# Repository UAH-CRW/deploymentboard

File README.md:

# deploymentboard
Deployment electronics design

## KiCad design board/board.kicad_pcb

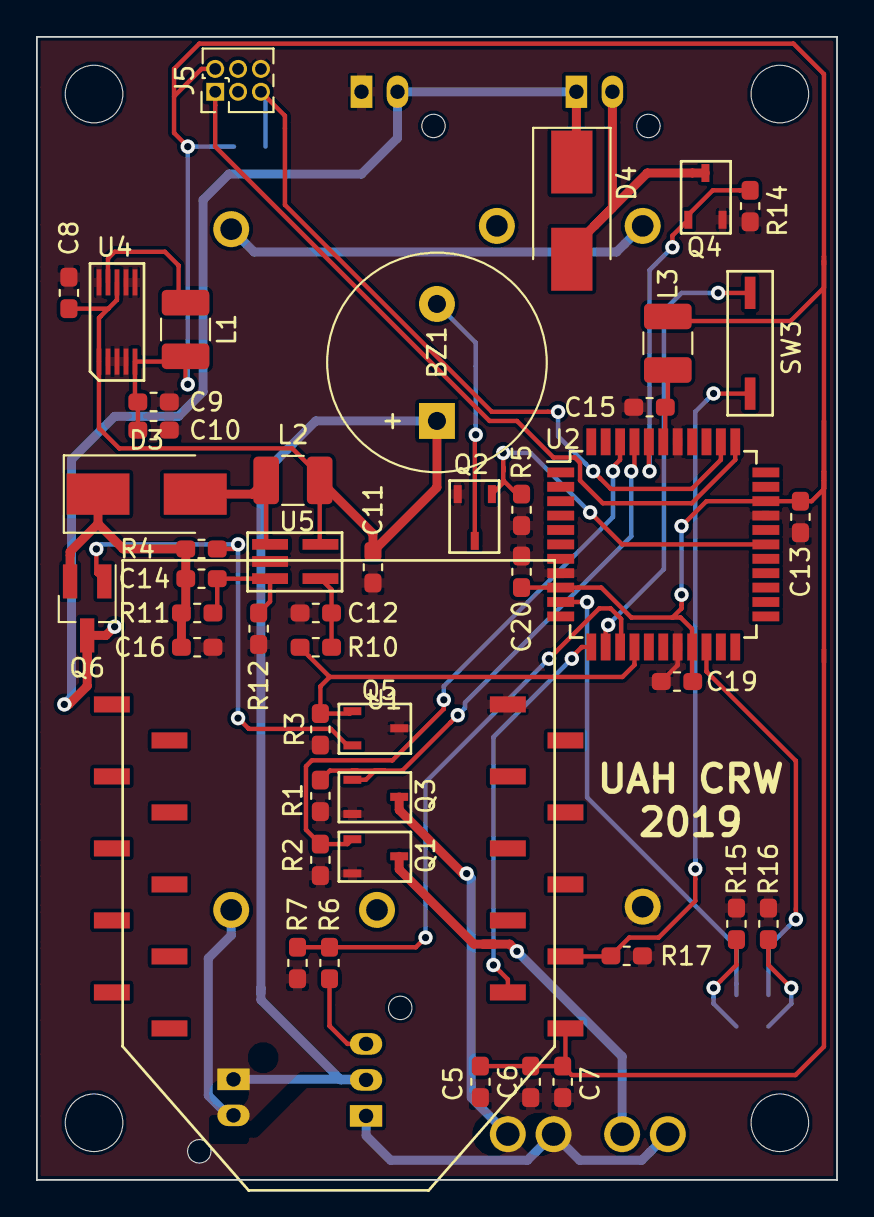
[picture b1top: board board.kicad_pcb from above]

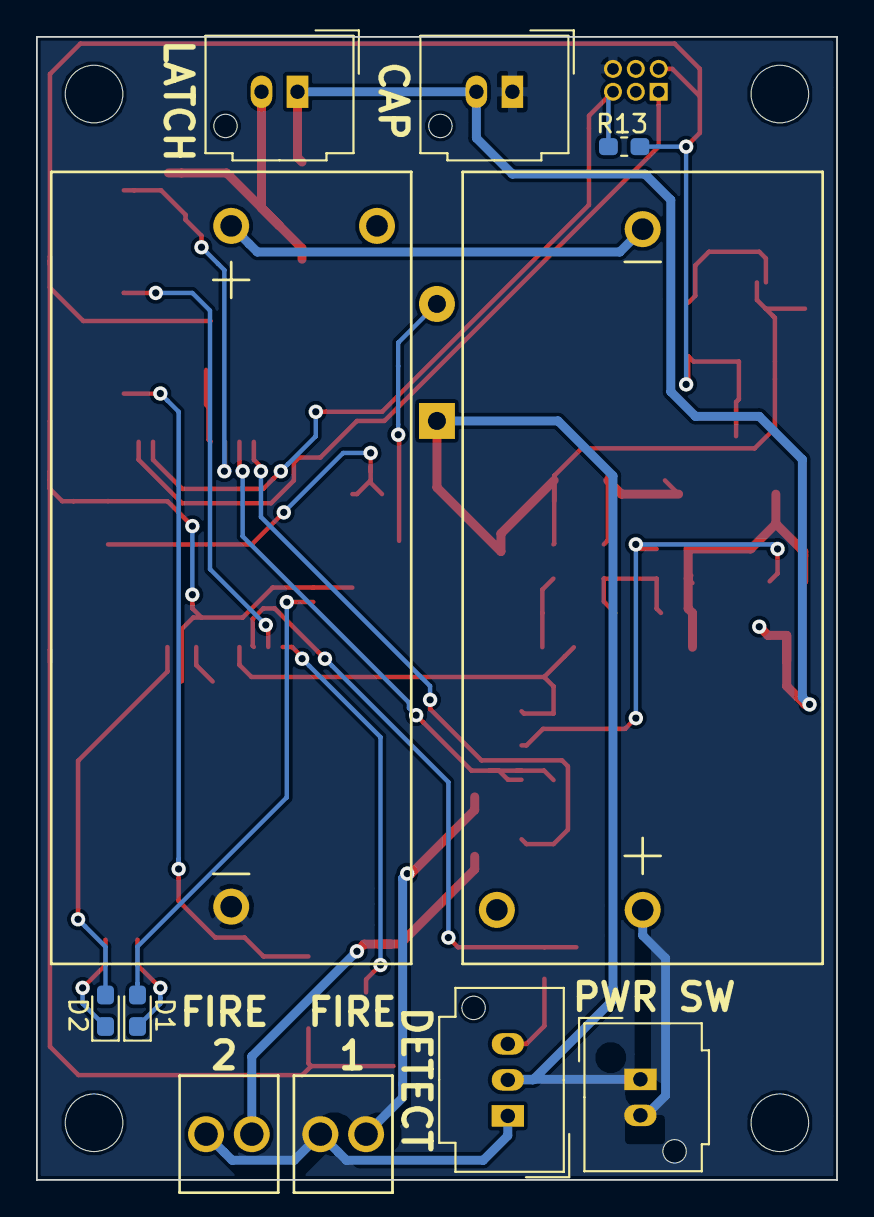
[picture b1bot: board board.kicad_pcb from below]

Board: 2 copper layers, 44.4 x 63.5 mm, 61 parts (11 on the bottom side), 34 nets.

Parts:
BT1, BT2: Battery; CR123A Battery Holder
BZ1: Buzzer; Buzzer_12x9.5RM7.6
C5, C8, C10: 10uF; C_0603_1608Metric_Pad1.05x0.95mm_HandSolder
C6, C11, C12: 1uF; C_0603_1608Metric_Pad1.05x0.95mm_HandSolder
C7: 47pF; C_0603_1608Metric_Pad1.05x0.95mm_HandSolder
C9: 22uF; C_0603_1608Metric_Pad1.05x0.95mm_HandSolder
C13, C15, C19, C20: 100nF; C_0603_1608Metric_Pad1.05x0.95mm_HandSolder
C14: 15pF; C_0603_1608Metric_Pad1.05x0.95mm_HandSolder
C16: 4.7uF; C_0603_1608Metric_Pad1.05x0.95mm_HandSolder
D1, D2: LED; LED_0603_1608Metric_Pad1.05x0.95mm_HandSolder
D3: D; D_SMB_Handsoldering
D4: D_Small; D_SMB_Handsoldering
J1, J3: Screw_Terminal_01x02; 2 pin 2.54mm screw terminal OSTVN02A150
J4, J6: Conn_01x02_Male; Molex_MicroClasp_55932-0210_1x02_P2.00mm_Vertical
J5: Conn_02x03_Odd_Even; PinHeader_2x03_P1.27mm_Vertical
L1: 10uH; L_1210_3225Metric_Pad1.42x2.65mm_HandSolder
L2: 4.7uH; L_1210_3225Metric_Pad1.42x2.65mm_HandSolder
L3: 27nH; L_1210_3225Metric_Pad1.42x2.65mm_HandSolder
MH1, MH2, MH3, MH4: MountingHole; MountingHole_3.2mm_M3
Q1, Q2, Q3, Q4, Q5: Q_NJFET_GSD; NFET Toshiba SSM3K339R
Q6: Q_PJFET_GSD; SOT-23_Handsoldering
R1, R2, R4, R5, R6, R7, R10, R13, R14, R17: 10k; R_0603_1608Metric_Pad1.05x0.95mm_HandSolder
R3: 10K; R_0603_1608Metric_Pad1.05x0.95mm_HandSolder
R11: 432k; R_0603_1608Metric_Pad1.05x0.95mm_HandSolder
R12: 49.9k; R_0603_1608Metric_Pad1.05x0.95mm_HandSolder
R15, R16: 220; R_0603_1608Metric_Pad1.05x0.95mm_HandSolder
SW1: SW_SPDT; Molex_MicroClasp_55932-0310_1x03_P2.00mm_Vertical
SW2: SW_SPDT; Molex_MicroClasp_55932-0210_1x02_P2.00mm_Vertical
SW3: SW_DIP_x01; DIP Switch CHS-01TA
U1: XBee; XBee_SMD
U2: ATxmega128A4U-AU; TQFP-44_10x10mm_P0.8mm
U4: IC_REG_BCK_3.3V; 10-pin FP TPS62056DGSR
U5: IC_REG_BOOST_ADJ_1.4A; IC REG BOOST SC4503TSKTRT

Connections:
+3V3: C5.2, C6.2, C7.2, C9.1, C10.1, C13.1, C19.1, C20.1, J5.2, L1.2, L3.1, R13.2, U1.1, U2.9, U2.19, U2.31, U4.5
+6V: BZ1.1, C8.1, C11.2, L2.1, SW1.2, SW2.1, U4.1, U4.8, U5.5
+12V: D4.1, J4.2, J6.1, Q6.3
/BUZZER_CTRL: Q2.1, R5.1, U2.28
/E_Match_Fire_1: Q3.1, R1.2, U2.41
/E_Match_Fire_2: Q1.1, R2.1, U2.42
/LATCH_ENABLE: Q5.1, R3.2, R10.2, U2.15
/LATCH_SENSE: R6.2, R7.2, U2.14
/LED1CTRL: D1.2, U2.10
/LED2CTRL: D2.2, U2.20
/PDI_CLK: J5.5, R13.1, U2.35
/PDI_DATA: J5.1, U2.34
/SOLENOID_CTRL: Q4.1, R14.1, U2.40
/USARTC0_RX: U1.2, U2.12
/USARTC0_TX: SW3.1, U2.13
GND: BT2.2, C5.1, C6.1, C7.1, C8.2, C9.2, C10.2, C11.1, C12.2, C13.2, C15.1, C16.2, C19.2, C20.2, J4.1, J5.6, Q1.2, Q2.2, Q3.2, Q4.2, Q5.3, R1.1, R2.2, R3.1, R5.2, R7.1, R12.2, R14.2, R15.1, R16.1, R17.2, U1.10, U2.8, U2.18, U2.30, U2.38, U4.2, U4.3, U4.4, U4.6, U4.7, U4.10, U5.2
unnamed: BT1.1, SW2.2
unnamed: BT1.2, BT2.1
unnamed: BZ1.2, Q2.3
unnamed: C12.1, R10.1, U5.4
unnamed: C14.1, C16.1, D3.1, Q6.2, R4.2, R11.1
unnamed: C14.2, R11.2, R12.1, U5.3
unnamed: C15.2, L3.2, U2.39
unnamed: D1.1, R15.2
unnamed: D2.1, R16.2
unnamed: D3.2, L2.2, U5.1
unnamed: D4.2, J6.2, Q4.3
unnamed: J1.1, Q3.3
unnamed: J1.2, J3.1, SW1.1
unnamed: J3.2, Q1.3
unnamed: L1.1, U4.9
unnamed: Q5.2, Q6.1, R4.1
unnamed: R6.1, SW1.3
unnamed: R17.1, SW3.2, U1.3

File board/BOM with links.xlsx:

Id | Designator | Package | Quantity | Designation | Supplier and ref
1 | J1,J3 | 2 pin 2.54mm screw terminal OSTVN02A150 | 2 | Screw_Terminal_01x02 | https://www.digikey.com/product-detail/en/on-shore-technolog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
2 | C20,C19,C3,C2,C1,C15,C13 | C_0603_1608Metric_Pad1.05x0.95mm_HandSolder | 7 | 100nF | https://www.digikey.com/product-detail/en/samsung-electro-me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
3 | J6 | JST_PH_B2B-PH-K_1x02_P2.00mm_Vertical | 1 | Conn_01x02_Male | https://www.digikey.com/product-detail/en/jst-sales-america-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
4 | D4 | D_SMB_Handsoldering | 1 | D_Small | https://www.digikey.com/product-detail/en/smc-diode-solution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
5 | R17,R14,R7,R13,R6,R4,R2,R1,R5,R10 | R_0603_1608Metric_Pad1.05x0.95mm_HandSolder | 9 | 10k | https://www.digikey.com/product-detail/en/susumu/RR0816P-103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
6 | SW3 | DIP Switch CHS-01TA | 1 | SW_DIP_x01 | https://www.digikey.com/product-detail/en/nidec-copal-electr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
7 | SW2 | JST_PH_B2B-PH-K_1x02_P2.00mm_Vertical | 1 | SW_SPDT | https://www.digikey.com/product-detail/en/jst-sales-america-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
8 | U1 | XBee_SMD | 2 | XBee | https://www.digikey.com/product-detail/en/sullins-connector-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
9 | C17,C18,C7 | C_0603_1608Metric_Pad1.05x0.95mm_HandSolder | 3 | 47pF | https://www.digikey.com/product-detail/en/avx-corporation/06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
10 | R15,R16 | R_0603_1608Metric_Pad1.05x0.95mm_HandSolder | 2 | 220 | https://www.digikey.com/product-detail/en/panasonic-electron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
11 | Q4,Q1,Q2,Q3 | NFET Toshiba SSM3K339R | 4 | Q_NJFET_GSD | https://www.digikey.com/product-detail/en/toshiba-semiconduc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
12 | J5 | PinHeader_2x03_P1.27mm_Vertical | 1 | Conn_02x03_Odd_Even | https://www.digikey.com/product-detail/en/sullins-connector-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
13 | BZ1 | Buzzer_12x9.5RM7.6 | 1 | Buzzer | https://www.digikey.com/product-detail/en/pui-audio-inc/AT-1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
14 | C10,C8,C5 | C_0603_1608Metric_Pad1.05x0.95mm_HandSolder | 3 | 10uF | https://www.digikey.com/product-detail/en/samsung-electro-me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
15 | C4,C16 | C_0603_1608Metric_Pad1.05x0.95mm_HandSolder | 2 | 4.7uF | https://www.digikey.com/product-detail/en/samsung-electro-me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
16 | C14 | C_0603_1608Metric_Pad1.05x0.95mm_HandSolder | 1 | 15pF | https://www.digikey.com/product-detail/en/yageo/CC0603JRNPO9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
17 | C12 | C_0603_1608Metric_Pad1.05x0.95mm_HandSolder | 1 | 1uF | https://www.digikey.com/product-detail/en/samsung-electro-me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
18 | C11,C6 | C_0603_1608Metric_Pad1.05x0.95mm_HandSolder | 2 | 1uF | https://www.digikey.com/product-detail/en/samsung-electro-me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
19 | C9 | C_0603_1608Metric_Pad1.05x0.95mm_HandSolder | 1 | 22uF | https://www.digikey.com/product-detail/en/samsung-electro-me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
20 | SW1 | JST_EH_B03B-EH-A_1x03_P2.50mm_Vertical | 1 | SW_SPDT | https://www.digikey.com/product-detail/en/jst-sales-america-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
21 | J2 | USB_Micro-B_Amphenol_10103594-0001LF_Horizontal | 1 | USB_B_Micro | https://www.digikey.com/product-detail/en/molex-llc/10516400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
22 | D3 | D_SOD-323 | 1 | D | https://www.digikey.com/product-detail/en/vishay-semiconduct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
23 | L1 | L_1210_3225Metric_Pad1.42x2.65mm_HandSolder | 1 | 10uH | https://www.digikey.com/product-detail/en/taiyo-yuden/LBC322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
24 | L2 | L_1210_3225Metric_Pad1.42x2.65mm_HandSolder | 1 | 4.7uH | https://www.digikey.com/product-detail/en/murata-electronics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
25 | L3 | L_1210_3225Metric_Pad1.42x2.65mm_HandSolder | 1 | 27nH | https://www.digikey.com/product-detail/en/tdk-corporation/NL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
26 | D1 | LED_0603_1608Metric_Pad1.05x0.95mm_HandSolder | 1 | LED - green | https://www.digikey.com/product-detail/en/rohm-semiconductor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
27 | D2 | LED_0603_1608Metric_Pad1.05x0.95mm_HandSolder | 1 | LED - red | https://www.digikey.com/product-detail/en/rohm-semiconductor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
28 | U3 | SSOP-16_3.9x4.9mm_P0.635mm | 1 | FT230XS | https://www.digikey.com/product-detail/en/ftdi-future-techno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
29 | R12 | R_0603_1608Metric_Pad1.05x0.95mm_HandSolder | 1 | 49.9k | https://www.digikey.com/product-detail/en/panasonic-electron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
30 | R11 | R_0603_1608Metric_Pad1.05x0.95mm_HandSolder | 1 | 432k | https://www.digikey.com/product-detail/en/yageo/RC0603FR-074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
31 | R9,R8 | R_0603_1608Metric_Pad1.05x0.95mm_HandSolder | 2 | 27 | https://www.digikey.com/product-detail/en/rohm-semiconductor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
32 | R3 | R_0603_1608Metric_Pad1.05x0.95mm_HandSolder | 1 | 47k | https://www.digikey.com/product-detail/en/yageo/RC0603JR-074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
33 | U4 | 10-pin FP TPS62056DGSR | 1 | IC_REG_BCK_3.3V | https://www.digikey.com/product-detail/en/texas-instruments/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
34 | BT1,BT2 | CR123A Battery Holder | 2 | Battery | https://www.digikey.com/product-detail/en/keystone-electroni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
35 | U5 | IC REG BOOST SC4503TSKTRT | 1 | IC_REG_BOOST_ADJ_1.4A | https://www.digikey.com/product-detail/en/semtech-corporatio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
36 | U2 | TQFP-44_10x10mm_P0.8mm | 1 | ATxmega128A4U-AU | https://www.digikey.com/product-detail/en/microchip-technolo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
 |  |  |  | Actual arming switch | https://www.digikey.com/product-detail/en/omron-electronics-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
 |  |  |  | Actual latch state switch | https://www.digikey.com/product-detail/en/e-switch/MS0850503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
 | JST Connectors on cable (01x02) |  |  |  | https://www.amazon.com/Shappy-Pieces-Connector-Silicone-Fema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
 | JST connectors on cable (01x03) |  |  |  | https://www.amazon.com/Micro-Connector-150mm-Cable-Female/dp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

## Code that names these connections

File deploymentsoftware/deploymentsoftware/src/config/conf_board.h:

/**
 * \file
 *
 * \brief User board configuration template
 *
 */
/*
 * Support and FAQ: visit <a href="https://www.microchip.com/support/">Microchip Support</a>
 */

#ifndef CONF_BOARD_H
#define CONF_BOARD_H

#define COMMS_USART						USARTC0
#define COMMS_USART_RX_ISR				USARTC0_RXC_vect
#define USART_TX_PIN					IOPORT_CREATE_PIN(PORTC, 3)
#define USART_RX_PIN					IOPORT_CREATE_PIN(PORTC, 2)
#define LATCH_ENABLE_PIN				IOPORT_CREATE_PIN(PORTC, 5)
#define SOLENOID_CTRL_PIN				IOPORT_CREATE_PIN(PORTA, 0)
#define LED_1_PIN						IOPORT_CREATE_PIN(PORTC, 0)
#define LED_2_PIN						IOPORT_CREATE_PIN(PORTD, 0)
#define EMATCH_PRIMARY_PIN				IOPORT_CREATE_PIN(PORTA, 1)
#define EMATCH_BACKUP_PIN				IOPORT_CREATE_PIN(PORTA, 2)
#define BUZZER_CTRL_PIN					IOPORT_CREATE_PIN(PORTE, 0)

#define LED_1_TC						TCC0
#define LED_1_TC_PORT					PORTC
#define LED_2_TC						TCD0
#define LED_2_TC_PORT					PORTD

#define BUZZER_INTERRUPT_TC				TCE0
#define BUZZER_INTERRUPT_SYSCLK_PORT	SYSCLK_PORT_E
#define BUZZER_INT_VECT					TCE0_OVF_vect

#define CLOCK_INTERRUPT_TC				TCD0
#define CLOCK_INTERRUPT_SYSCLK_PORT		SYSCLK_PORT_D
#define CLOCK_INT_VECT					TCD0_OVF_vect

#define CAP_ADC							ADCA
#define CAP_CHANNEL						ADC_CH0
#define CAP_SENSE_PIN					ADCCH_POS_PIN6
#define CAP_VDIVIDE_FACTOR				9.1818f

#endif // CONF_BOARD_H

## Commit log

2018-10-26 MCU and firing circuits
2018-11-11 Added USB connector and FTDI chip
2018-11-12 12V converter
2018-11-12 Firing circuits, XBee, indicators
2018-11-13 3.3V supply, MCU power connections
2018-11-13 Made schematic prettier, changed to 8.5x11 paper
2018-11-13 Added PDI port
2018-11-14 Footprints for XBee and voltage regulators
2018-11-14 Added solenoid for latch
    Because that's important. Whoopsie
2018-11-30 Fixed issues Elena identified in her review
2018-12-09 Fixed footprints, major placements
2018-12-09 Finished placement, began routing
2018-12-10 Routed :)
2018-12-13 Work on BOM (incomplete)
2018-12-17 Added component values for soft-start RC filter
2019-02-03 Fixed solenoid MOSFET hookup
2019-02-05 Initial software creation
    No testing
2019-02-05 SW Updates
2019-02-05 Reverted to having 12V supply
2019-02-06 E-match test software revision
2019-02-07 Diode, MOSFET, 3-pin JST plug fixes
2019-02-07 Fixed buzzer hole spacing
2019-02-13 Fixed PCB for rev2
2019-03-03 Software updates for hardware rev2
2019-03-12 Trying to detect solenoid extension
2019-03-14 Solenoid position detection
